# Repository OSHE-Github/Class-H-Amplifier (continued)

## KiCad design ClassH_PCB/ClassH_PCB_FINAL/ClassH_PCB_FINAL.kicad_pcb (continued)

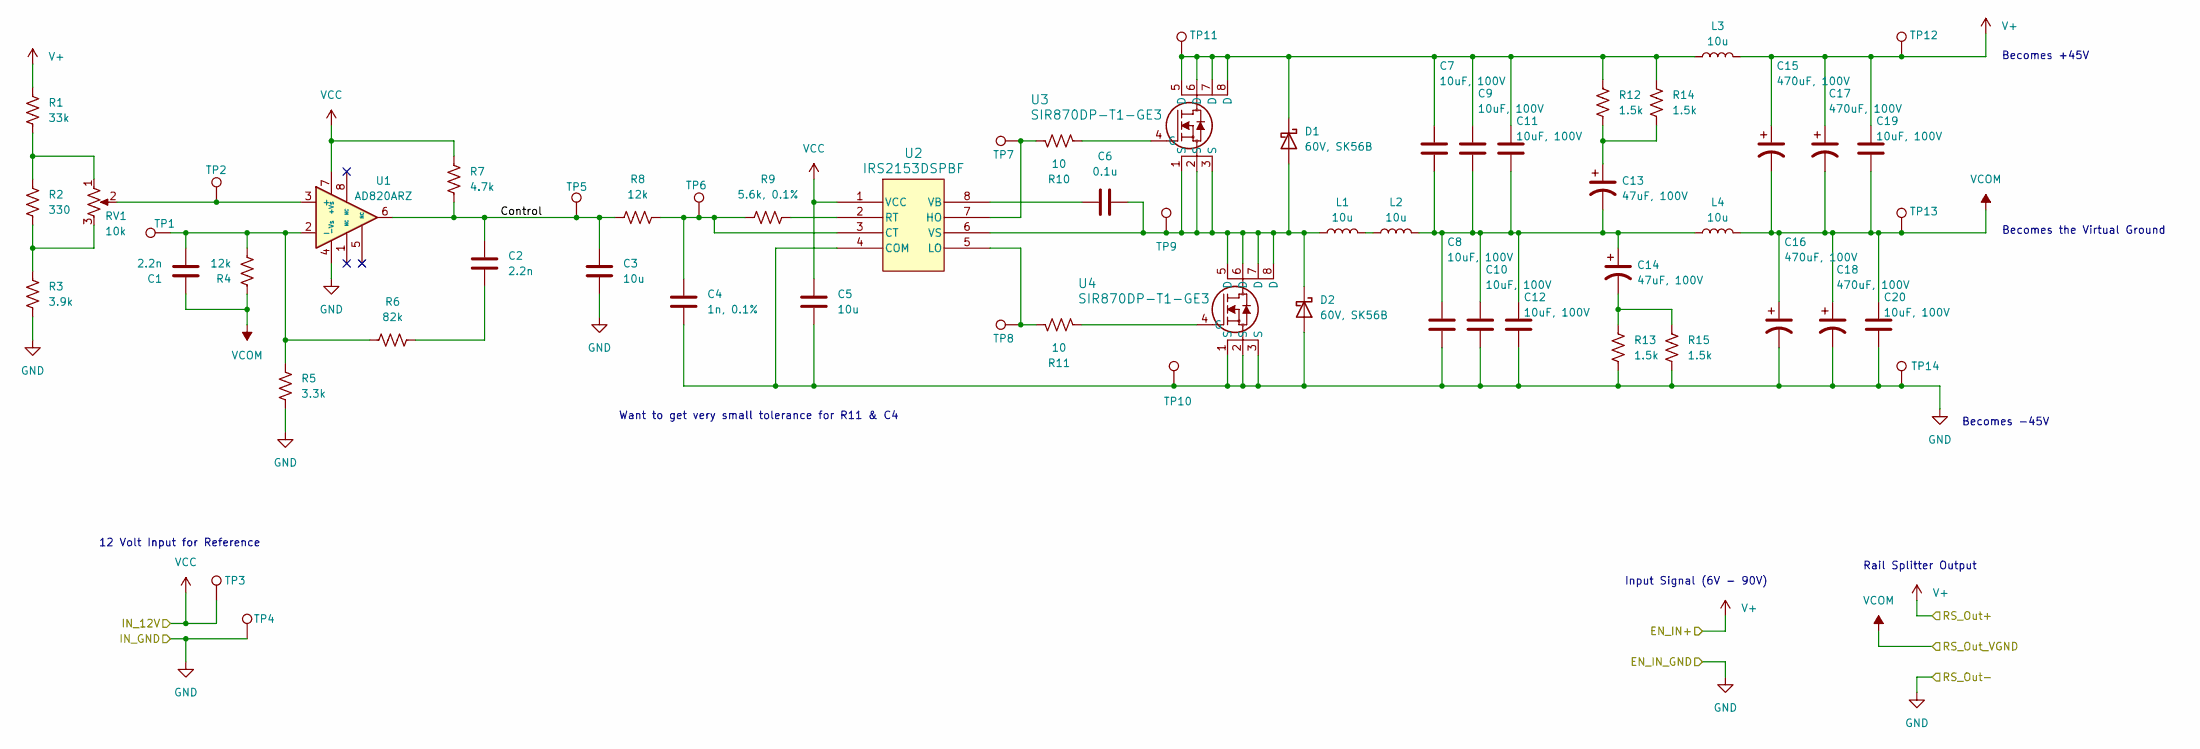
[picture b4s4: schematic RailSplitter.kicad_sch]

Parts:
C1, C2: 2.2n; C_0603_1608Metric_Pad1.08x0.95mm_HandSolder
C3, C5: 10u; C_0805_2012Metric_Pad1.18x1.45mm_HandSolder
C4: 1n, 0.1%; C_0603_1608Metric_Pad1.08x0.95mm_HandSolder
C6: 0.1u; C_0603_1608Metric_Pad1.08x0.95mm_HandSolder
C7, C8, C9, C10, C11, C12, C19, C20: 10uF, 100V; C_1210_3225Metric_Pad1.33x2.70mm_HandSolder
C13, C14: 47uF, 100V; CP_Radial_D10.0mm_P5.00mm
C15, C16, C17, C18: 470uF, 100V; CP_Radial_D16.0mm_P7.50mm
D1, D2: 60V, SK56B; D_SMB_Handsoldering
L1, L2, L3, L4: 10u; IND_ETQP5M100YFC
R1: 33k; R_0603_1608Metric_Pad0.98x0.95mm_HandSolder
R2: 330; R_0603_1608Metric_Pad0.98x0.95mm_HandSolder
R3: 3.9k; R_0603_1608Metric_Pad0.98x0.95mm_HandSolder
R4, R8: 12k; R_0603_1608Metric_Pad0.98x0.95mm_HandSolder
R5: 3.3k; R_0603_1608Metric_Pad0.98x0.95mm_HandSolder
R6: 82k; R_0603_1608Metric_Pad0.98x0.95mm_HandSolder
R7: 4.7k; R_0603_1608Metric_Pad0.98x0.95mm_HandSolder
R9: 5.6k, 0.1%; R_0603_1608Metric_Pad0.98x0.95mm_HandSolder
R10, R11: 10; R_0603_1608Metric_Pad0.98x0.95mm_HandSolder
R12, R13, R14, R15: 1.5k; R_0603_1608Metric_Pad0.98x0.95mm_HandSolder
RV1: 10k; Potentiometer_Bourns_TC33X_Vertical
TP1, TP2, TP3, TP4, TP5, TP6, TP7, TP8, TP9, TP10, TP11, TP12, TP13, TP14: TestPoint; TestPoint_Keystone_5005-5009_Compact
U1: AD820ARZ; SOIC127P600X175-8N; MPN AD820ARZ-REEL-REEL7
U2: IRS2153DSPBF; SOIC8_INF
U3, U4: SIR870DP-T1-GE3; MOSFET_7DP-T1-GE3_VIS

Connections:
/RailSplitter/Control: C2.1, C3.1, R7.2, R8.1, TP5.1, U1.6
GND: C3.2, C4.2, C5.2, C8.1, C10.1, C12.1, C16.2, C18.2, C20.1, D2.2 (A), R3.1, R5.1, R13.1, R15.1, TP4.1, TP10.1, TP14.1, U1.4 (-Vs), U2.4 (COM), U4.1 (S), U4.2 (S), U4.3 (S); also elsewhere on the board
unnamed: C2.2, R6.2
unnamed: C7.1, C8.2, C9.1, C10.2, C11.1, C12.2, C13.2, C14.1, L2.2, L4.1
unnamed: C13.1, R12.1, R14.1
unnamed: C14.2, R13.2, R15.2
unnamed: C6.2, D1.2 (A), D2.1 (K), L1.1, TP9.1, U2.6 (VS), U3.1 (S), U3.2 (S), U3.3 (S), U4.5 (D), U4.6 (D), U4.7 (D), U4.8 (D)
unnamed: C7.2, C9.2, C11.2, D1.1 (K), L3.1, R12.2, R14.2, TP11.1, U3.5 (D), U3.6 (D), U3.7 (D), U3.8 (D)
unnamed: L1.2, L2.1
unnamed: R1.2, R2.2, RV1.1
unnamed: R2.1, R3.2, RV1.3
unnamed: RV1.2, TP2.1, U1.3 (+)
unnamed: C1.2, R4.1, R5.2, R6.1, TP1.1, U1.2 (-)
unnamed: C4.1, R8.2, R9.1, TP6.1, U2.3 (CT)
unnamed: R10.1, TP7.1, U2.7 (HO)
unnamed: R11.1, TP8.1, U2.5 (LO)
unnamed: R9.2, U2.2 (RT)
unnamed: C6.1, U2.8 (VB)
unnamed: R10.2, U3.4 (G)
unnamed: R11.2, U4.4 (G)
V+: C15.1, C17.1, C19.2, L3.2, R1.1, TP12.1; also elsewhere on the board
VCC: C5.1, R7.1, TP3.1, U1.7 (+Vs), U2.1 (VCC); also elsewhere on the board
VCOM: C1.1, C15.2, C16.1, C17.2, C18.1, C19.1, C20.2, L4.2, R4.2, TP13.1; also elsewhere on the board

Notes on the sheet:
Want to get very small tolerance for R11 & C4
Becomes +45V
Rail Splitter Output
Becomes -45V
Becomes the Virtual Ground
12 Volt Input for Reference
Input Signal (6V - 90V)

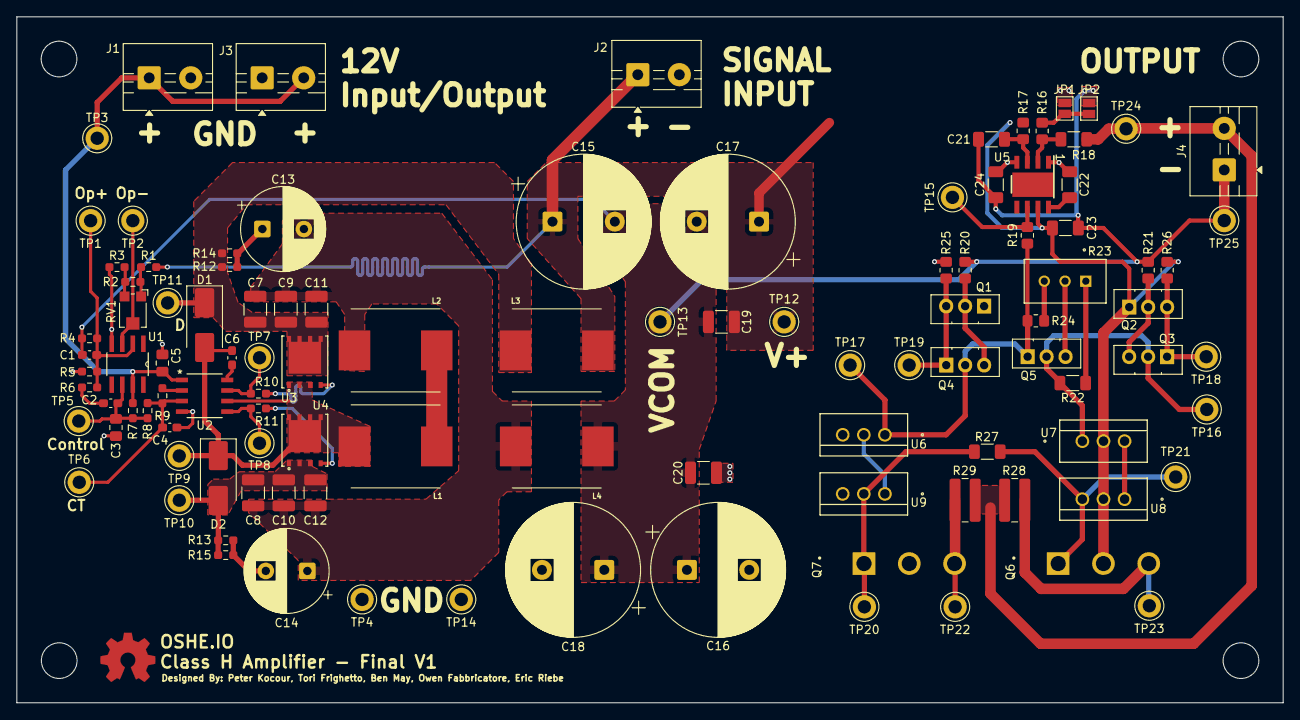
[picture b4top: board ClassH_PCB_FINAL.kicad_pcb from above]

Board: 2 copper layers, 152.4 x 82.6 mm, 107 parts (0 on the bottom side), 46 nets.

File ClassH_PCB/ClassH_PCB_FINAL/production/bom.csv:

Designator,Footprint,Quantity,Value,LCSC Part #
"C1, C2",0603,2,2.2n,
"C10, C11, C12, C19, C20, C7, C8, C9",1210,8,"10uF, 100V",
"C13, C14",CP_Radial_D10.0mm_P5.00mm,2,"47uF, 100V",
"C15, C16, C17, C18",CP_Radial_D16.0mm_P7.50mm,4,"470uF, 100V",
C21,1206,1,1n,
C22,1206,1,30p,
"C23, C24",1206,2,0.1u,
"C3, C5",0805,2,10u,
C4,0603,1,"1n, 0.1%",
C6,0603,1,0.1u,
"D1, D2",D_SMB_Handsoldering,2,"60V, SK56B",
"J1, J2, J3, J4",TerminalBlock_MaiXu_MX126-5.0-02P_1x02_P5.00mm,4,Conn_01x02,
"L1, L2, L3, L4",IND_ETQP5M100YFC,4,10u,
"Q1, Q4, Q5",TO-126-3_Vertical,3,Q_NPN_ECB,
"Q2, Q3",TO-126-3_Vertical,2,Q_PNP_ECB,
Q6,TO545P2030X530X2900-3,1,MJL21194,
Q7,TO545P2030X530X2900-3,1,MJL21193G,
R1,0603,1,33k,
"R10, R11",0603,2,10,
"R12, R13, R14, R15",0603,4,1.5k,
"R16, R17",0805,2,1k,
R18,1206,1,20k,
"R19, R25, R26",0805,3,100,
R2,0603,1,330,
"R20, R21",0805,2,40k,
R22,1206,1,3.6k,
R23,POT_PV36W_MUR,1,PV36W102C01B00,
R24,0805,1,1.1k,
R27,1206,1,330,
"R28, R29",1020,2,0.33,
R3,0603,1,3.9k,
"R4, R8",0603,2,12k,
R5,0603,1,3.3k,
R6,0603,1,82k,
R7,0603,1,4.7k,
R9,0603,1,"5.6k, 0.1%",
RV1,Potentiometer_Bourns_TC33X_Vertical,1,10k,
"TP1, TP10, TP11, TP12, TP13, TP14, TP15, TP16, TP17, TP18, TP19, TP2, TP20, TP21, TP22, TP23, TP24, TP25, TP3, TP4, TP5, TP6, TP7, TP8, TP9",TestPoint_Keystone_5005-5009_Compact,25,TestPoint,
U1,SOIC127P600X175-8N,1,AD820ARZ,AD820ARZ-REEL-REEL7
U2,SOIC8_INF,1,IRS2153DSPBF,
"U3, U4",MOSFET_7DP-T1-GE3_VIS,2,SIR870DP-T1-GE3,
U5,DDA0008J_NV,1,OPA454AIDDA,
"U6, U9",TO-220AB_ONS,2,MJE15033G,
"U7, U8",TO-220AB_ONS,2,MJE15032G,

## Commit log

2026-04-18 Added ClassH PCB Files
2026-04-21 Rename block_diagram.png to Media/block_diagram.png
2026-04-22 Rename Class H Report.pdf to Documents/Class H Report.pdf
